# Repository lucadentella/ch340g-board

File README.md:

# CH340G minimal board

First version -> http://www.lucadentella.it/en/2017/06/15/ch340g-board/
Updated version -> http://www.lucadentella.it/en/2017/07/17/aggiornamento-per-la-ch340g-board/

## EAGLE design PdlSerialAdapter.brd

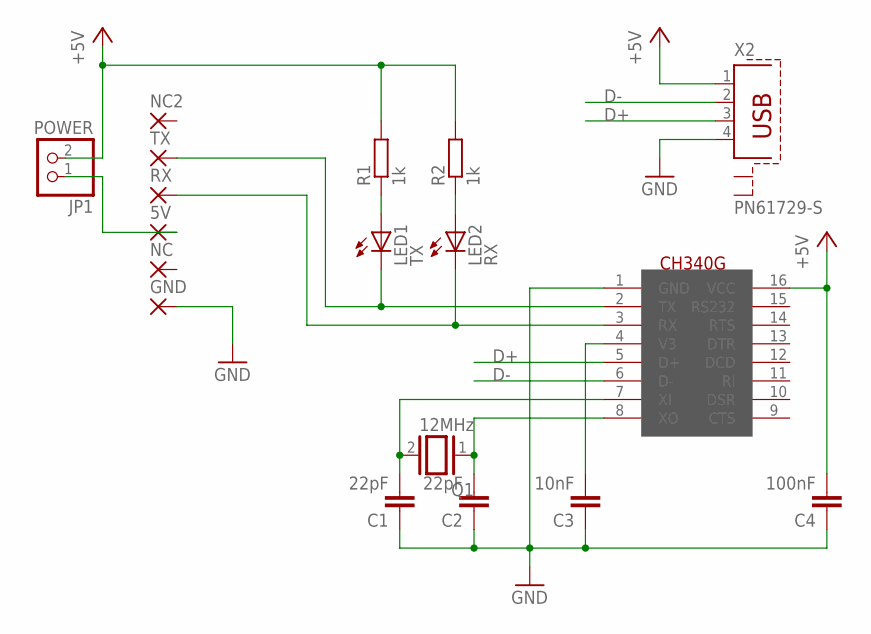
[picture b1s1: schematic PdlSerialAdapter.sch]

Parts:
5V: SMD2; SMD1,27-2,54
C1, C2: 22pF; C025-025X050
C3: 10nF; C050-030X075
C4: 100nF; C050-030X075
GND: SMD2; SMD1,27-2,54
JP1: POWER; 1X02
LED1: TX; LED3MM
LED2: RX; LED3MM
NC, NC2: SMD2; SMD1,27-2,54
Q1: 12MHz; QS
R1, R2: 1k; 0207/2V
RX: SMD2; SMD1,27-2,54
TX: SMD2; SMD1,27-2,54
U$1: CH340G; SOIC16
X2: PN61729-S

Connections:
+5V: C4.2, JP1.2, R1.2, R2.2, U$1.16 (VCC), X2.1
D+: U$1.5 (D+), X2.3
D-: U$1.6 (D-), X2.2
GND: C1.1, C2.1, C3.1, C4.1, GND.1, U$1.1 (GND), X2.4
unnamed: C1.2, Q1.2, U$1.7 (XI)
unnamed: C2.2, Q1.1, U$1.8 (XO)
unnamed: 5V.1, JP1.1
unnamed: C3.2, U$1.4 (V3)
unnamed: LED1.K (C), TX.1, U$1.2 (TX)
unnamed: LED1.A, R1.1
unnamed: LED2.A, R2.1
RX: LED2.K (C), RX.1, U$1.3 (RX)

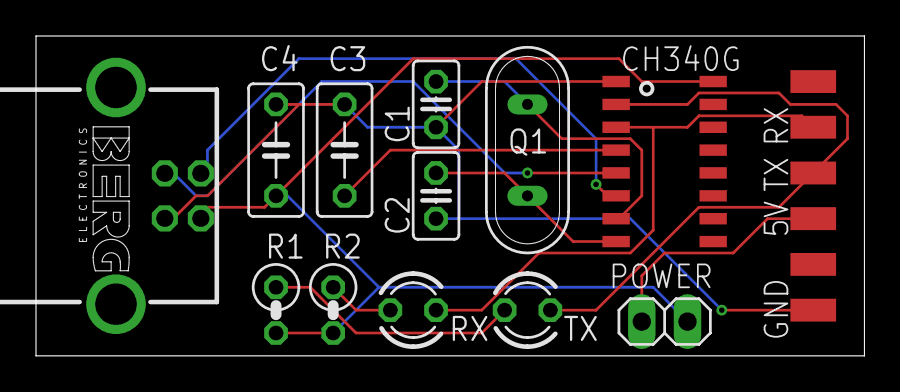
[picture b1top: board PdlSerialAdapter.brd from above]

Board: 2 copper layers, 46.0 x 17.8 mm, 18 parts (0 on the bottom side), 12 nets.

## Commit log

2017-06-13 First version
2017-07-17 New version
